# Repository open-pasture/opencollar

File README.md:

# OpenCollar

Open hardware virtual-fence collar. Off-the-shelf parts, open protocol, works with any software that speaks it.

Two collar types share as much as possible:

- **Rook** — base-station collar (LTE-M + GPS, larger battery)
- **Starling** — cheaper LoRa mesh-relay collar

## Repo map

| Path | What |
| --- | --- |
| [`docs/REPO-STRUCTURE.md`](docs/REPO-STRUCTURE.md) | Layout, old→new moves, conventions, firmware target split |
| [`docs/rook/`](docs/rook/) | Rook collar docs (flash / control / provision placeholders) |
| [`docs/starling/`](docs/starling/) | Starling collar docs (same) |
| [`docs/assembly/`](docs/assembly/) | Assembly pointers |
| [`docs/firmware/`](docs/firmware/) | Pilot firmware spec and Rook gap list |
| [`hardware/common/`](hardware/common/) | Shared CAD (`dims`, strap/clamp/insert), shared STLs |
| [`hardware/rook/`](hardware/rook/) | Rook Node V1 CAD, STLs, print profiles, fit audit |
| [`hardware/starling/`](hardware/starling/) | Starling skeleton (reuses common) |
| [`hardware/carrier/`](hardware/carrier/) | Carrier PCB |
| [`firmware/`](firmware/) | Zephyr firmware (see [`firmware/ARCHITECTURE.md`](firmware/ARCHITECTURE.md) for target layout) |
| [`protocol/`](protocol/) | Wire protocol and vectors |

### Design and build docs

- `docs/BUILD-LOG.md` — dated record of every step, result, and decision
- `docs/WELFARE-POLICY.md` — cue limits, auto shut-off, and welfare events (review thresholds before pulse)
- `docs/SHOCK-MODULE-INTERFACE.md` — reserved shock/pulse interface (side pods; OFF until named reviewer + Cody approve)
- `docs/PROTOTYPE-V0.md` — current state of the V0 prototype
- `docs/V1-DESIGN.md` — the V1 collar design and cost estimates
- `docs/MANUFACTURING.md` — how we get to 1,000 collars, and why FCC and carrier approval matter
- `docs/BOARD-DESIGN.md` — designing the custom board on a small budget
- `docs/DESIGN-PHASE.md` — board design toolchain and workflow (KiCad + SKiDL)
- `docs/COLLAR-FIRST-PRINCIPLES.md` — the slim collar worked out from first principles
- `docs/TEST-FIXTURE.md` — how every board gets tested, explained from zero, with pictures
- `docs/CARRIER-EXPLAINED.md` — every part on the carrier board, what it does, and where it sits in the collar
- `docs/STRATEGY.md` — product strategy and licensing
- `hardware/prototype-cart.md` — parts for the first prototype
- `hardware/orders-2026-09-26.md` — what was ordered and paid
- `hardware/tools.md` — tools for building a collar
- `hardware/bom.md` — parts list
- `hardware/photos/` — build photos

## Licence

OpenCollar is open so anyone can build, repair and improve their own collar.

| What | Licence | Folders |
| --- | --- | --- |
| Firmware, scripts and the protocol | [Apache-2.0](LICENSE) | `firmware/`, `protocol/`, and code anywhere else |
| Hardware and CAD (boards, enclosure, print files) | [CERN-OHL-W-2.0](LICENSES/CERN-OHL-W-2.0.txt) | `hardware/` |
| Docs, photos and renders | [CC BY 4.0](LICENSES/CC-BY-4.0.txt) | `docs/`, `hardware/photos/`, `hardware/*/renders/` |

In plain terms:

- **Firmware and protocol:** use them for anything, including closed products. Keep the copyright notice and [NOTICE](NOTICE).
- **Hardware:** build, sell and change the boards and the enclosure. If you ship a modified version of these design files, publish your changes to them under the same licence. Your own add-ons can stay closed.
- **Docs:** reuse them with credit to openpasture.

Third-party files keep their own licences: `firmware/boards/makerdiary/` (Apache-2.0, plus Nordic's 5-clause licence where its headers say so) and `firmware/third_party/monocypher/` (CC0 or BSD-2-Clause).

The names openpasture and OpenCollar and the openpasture logo aren't covered by these licences; see [NOTICE](NOTICE). Contributing: [CONTRIBUTING.md](CONTRIBUTING.md).

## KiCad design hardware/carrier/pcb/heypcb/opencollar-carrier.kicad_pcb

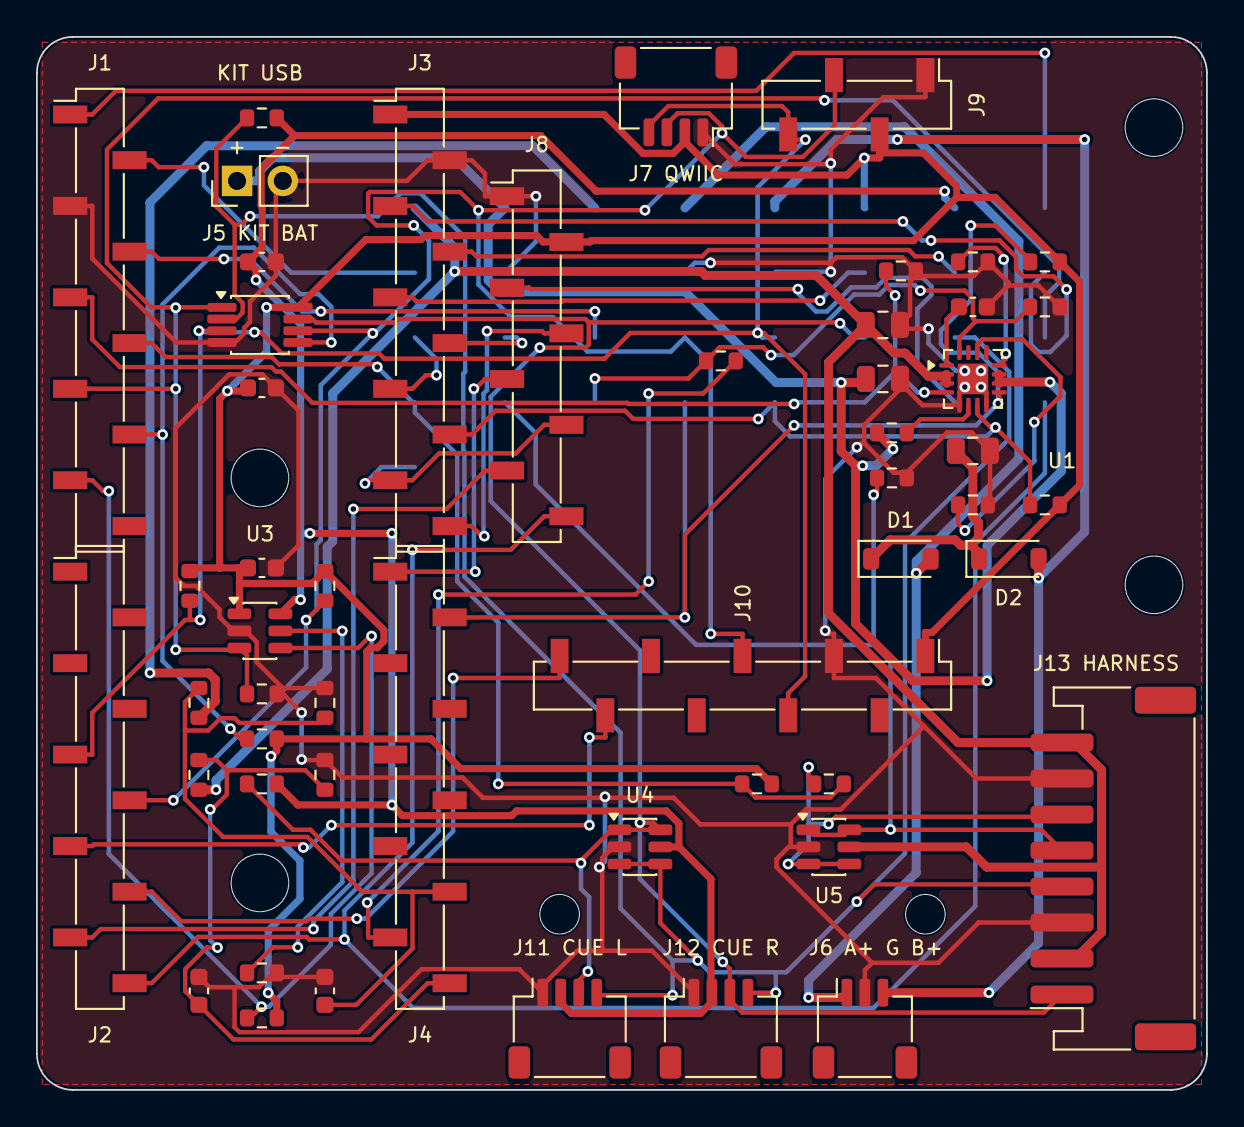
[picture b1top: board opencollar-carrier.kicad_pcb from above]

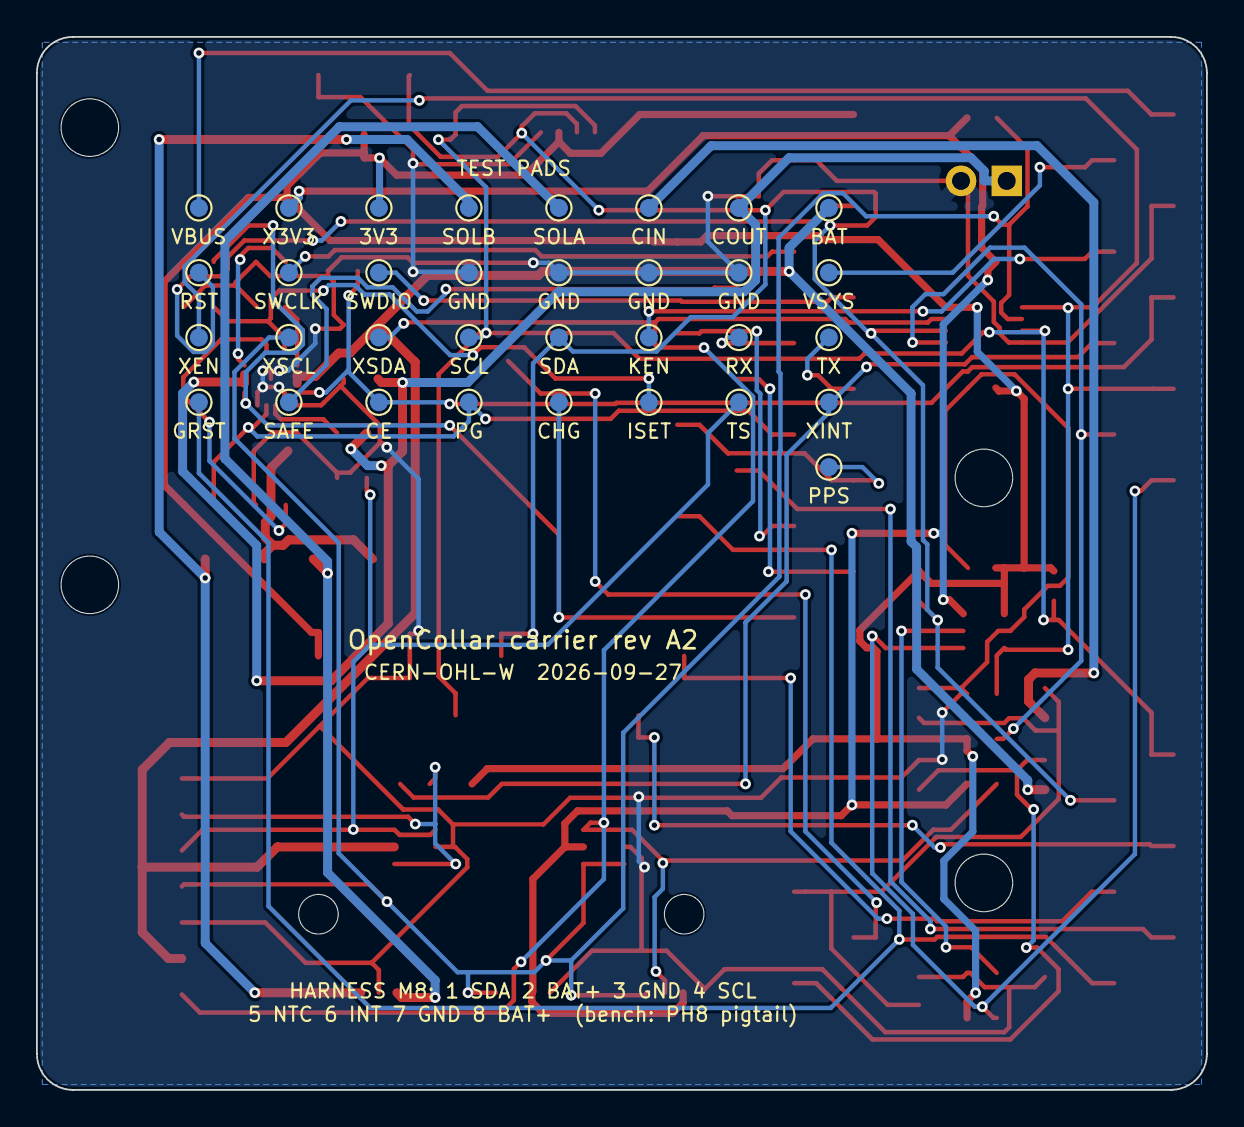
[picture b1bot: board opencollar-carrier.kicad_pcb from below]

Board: 2 copper layers, 65.0 x 58.5 mm, 91 parts (33 on the bottom side), 45 nets.

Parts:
C1: 10n; C_0603_1608Metric
C2, C3, C4: 10u/25V; C_0805_2012Metric
C5, C6, C7: 100n; C_0603_1608Metric
C8, C9: 1u; C_0603_1608Metric
D1, D2: B5819W; D_SOD-123
H1, H2, H3, H4: MountingHole; MountingHole_3.2mm_M3
H5, H6: MountingHole; MountingHole_2.2mm_M2
J1: Kit 1-10; PinSocket_1x10_P2.54mm_Vertical_SMD_Pin1Left
J2: Kit 11-20; PinSocket_1x10_P2.54mm_Vertical_SMD_Pin1Left
J3: Kit 40-31; PinSocket_1x10_P2.54mm_Vertical_SMD_Pin1Left
J4: Kit 30-21; PinSocket_1x10_P2.54mm_Vertical_SMD_Pin1Left
J5: Kit J2 feed; PinHeader_1x02_P2.54mm_Vertical
J6: Panels A/GND/B; JST_SH_SM03B-SRSS-TB_1x03-1MP_P1.00mm_Horizontal
J7: Qwiic spare; JST_SH_SM04B-SRSS-TB_1x04-1MP_P1.00mm_Horizontal
J8: M10S J5; PinSocket_1x08_P2.54mm_Vertical_SMD_Pin1Left
J9: M10S J3; PinSocket_1x04_P2.54mm_Vertical_SMD_Pin1Left
J10: ISM330; PinSocket_1x09_P2.54mm_Vertical_SMD_Pin1Left
J11: Cue L; JST_SH_SM04B-SRSS-TB_1x04-1MP_P1.00mm_Horizontal
J12: Cue R; JST_SH_SM04B-SRSS-TB_1x04-1MP_P1.00mm_Horizontal
J13: Harness M8; JST_PH_S8B-PH-SM4-TB_1x08-1MP_P2.00mm_Horizontal
R1, R5, R17: 10k; R_0603_1608Metric
R2: 887; R_0603_1608Metric
R3: 3.24k; R_0603_1608Metric
R4: 71.5k; R_0603_1608Metric
R6, R7, R8, R13, R16, R20, R21, R23: 100k; R_0603_1608Metric
R9, R10, R11: 1M; R_0603_1608Metric
R12: 200k; R_0603_1608Metric
R14, R15, R18, R19: 4.7k; R_0603_1608Metric
R22: 1k; R_0603_1608Metric
TP1: BAT; TestPoint_Pad_D1.0mm
TP2: CHG_OUT; TestPoint_Pad_D1.0mm
TP3: CHG_IN; TestPoint_Pad_D1.0mm
TP4: SOLAR_A; TestPoint_Pad_D1.0mm
TP5: SOLAR_B; TestPoint_Pad_D1.0mm
TP6: 3V3; TestPoint_Pad_D1.0mm
TP7: EXT_3V3; TestPoint_Pad_D1.0mm
TP8: KIT_VBUS; TestPoint_Pad_D1.0mm
TP9: KIT_VSYS; TestPoint_Pad_D1.0mm
TP10, TP11, TP12, TP13: GND; TestPoint_Pad_D1.0mm
TP14: SWDIO; TestPoint_Pad_D1.0mm
TP15: SWCLK; TestPoint_Pad_D1.0mm
TP16: RESET; TestPoint_Pad_D1.0mm
TP17: UART_TX; TestPoint_Pad_D1.0mm
TP18: UART_RX; TestPoint_Pad_D1.0mm
TP19: KIT_EN; TestPoint_Pad_D1.0mm
TP20: I2C_SDA; TestPoint_Pad_D1.0mm
TP21: I2C_SCL; TestPoint_Pad_D1.0mm
TP22: EXT_SDA; TestPoint_Pad_D1.0mm
TP23: EXT_SCL; TestPoint_Pad_D1.0mm
TP24: EXT_EN; TestPoint_Pad_D1.0mm
TP25: EXT_INT; TestPoint_Pad_D1.0mm
TP26: TS; TestPoint_Pad_D1.0mm
TP27: ISET; TestPoint_Pad_D1.0mm
TP28: CHG_STAT; TestPoint_Pad_D1.0mm
TP29: CHG_PGOOD; TestPoint_Pad_D1.0mm
TP30: CHG_CE; TestPoint_Pad_D1.0mm
TP31: GNSS_SAFEBOOT; TestPoint_Pad_D1.0mm
TP32: GNSS_RESET_N; TestPoint_Pad_D1.0mm
TP33: GNSS_PPS; TestPoint_Pad_D1.0mm
U1: BQ24074RGT; VQFN-16-1EP_3x3mm_P0.5mm_EP1.68x1.68mm
U2: TCA4307; VSSOP-8_3x3mm_P0.65mm
U3: TPS2553; SOT-23-6
U4, U5: USBLC6-2SC6; SOT-23-6

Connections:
3V3: C7.1, C8.1, J3.1, J7.2, J8.2, J9.2, J10.1, R7.2, R8.2, R14.2, R15.2, R17.2, R21.2, R23.2, TP6.1, U2.8, U3.1
BAT: C4.1, J13.2, J13.8, R9.1, TP1.1, U1.2, U1.3, U5.5
CHG_CE: J1.5, R6.1, TP30.1, U1.4
CHG_IN: C2.1, D1.1, D2.1, R11.1, TP3.1, U1.13
CHG_OUT: C3.1, J5.1, R1.1, TP2.1, U1.10, U1.11
CHG_PGOOD: J3.8, R8.1, TP29.1, U1.7
CHG_STAT: J4.2, R7.1, TP28.1, U1.9
EXT_3V3: C9.1, J11.2, J12.2, R18.2, R19.2, TP7.1, U3.6, U4.5
EXT_EN: J1.7, R16.1, TP24.1, U2.1, U3.3
EXT_FAULT: J1.9, R21.1, U3.4
EXT_INT: J1.6, R22.2, R23.1, TP25.1
EXT_INT_RAW: J13.6, R22.1, U5.3, U5.4
EXT_READY: J1.8, R17.1, U2.5
EXT_SCL: J11.4, J12.4, J13.4, R19.1, TP23.1, U2.2, U4.3, U4.4
EXT_SDA: J11.3, J12.3, J13.1, R18.1, TP22.1, U2.7, U4.1, U4.6
GND: C1.2, C2.2, C3.2, C4.2, C5.2, C6.2, C7.2, C8.2, C9.2, J1.3, J3.2, J5.2, J6.2, J7.1, J8.1, J9.1, J10.3, J11.1, J12.1, J13.3, J13.7, R2.2, R3.2, R4.2, R5.2, R6.2, R10.2, R12.2, R16.2, R20.2, TP10.1, TP11.1, TP12.1, TP13.1, U1.5, U1.8, U1.17, U2.4, U3.2, U4.2, U5.2
GNSS_EXTINT: J2.9, J8.7
GNSS_PPS: J3.9, J8.6, TP33.1
GNSS_RESET_N: J2.10, J8.8, TP32.1
GNSS_RXD: J4.1, J8.5
GNSS_SAFEBOOT: J8.3, TP31.1
GNSS_TXD: J3.10, J8.4
I2C_SCL: J2.5, J7.4, J9.4, J10.4, R15.1, TP21.1, U2.3
I2C_SDA: J2.6, J7.3, J9.3, J10.5, R14.1, TP20.1, U2.6
IMU_INT1: J2.7, J10.8
IMU_INT2: J2.8, J10.9
ISET: R2.1, R13.1, TP27.1, U1.16
ISET_SENSE: J4.9, R13.2
KIT_EN: J1.4, TP19.1
KIT_VBUS: J1.1, TP8.1
KIT_VSYS: J1.2, TP9.1
unnamed: R1.2, U1.6
unnamed: R3.1, U1.12
unnamed: R4.1, U1.14
unnamed: R20.1, U3.5
RESET: J3.3, TP16.1
SOLAR_A: D1.2, J6.1, TP4.1
SOLAR_B: D2.2, J6.3, TP5.1
SWCLK: J3.4, TP15.1
SWDIO: J3.5, TP14.1
TS: C1.1, J13.5, R5.1, TP26.1, U1.1, U5.1, U5.6
UART_RX: J3.6, TP18.1
UART_TX: J3.7, TP17.1
VBAT_SENSE: C5.1, J4.10, R9.2, R10.1
VIN_SENSE: C6.1, J4.8, R11.2, R12.1

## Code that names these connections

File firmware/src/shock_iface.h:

/*
 * Shock / pulse module — names and states only.
 *
 * Reservation: docs/SHOCK-MODULE-INTERFACE.md, protocol/registry.md.
 * Placement (Cody): side pods. This header must not grow functions that
 * drive any output. No welfare reviewer is named yet — module stays OFF
 * in all builds until one is named and Cody approves. Dual enable /
 * GATE_LATCH / pulse_grant are proposed, awaiting Cody. Default is off;
 * not_fitted / unknown means no path may drive HV.
 */
#ifndef OPENCOLLAR_SHOCK_IFACE_H
#define OPENCOLLAR_SHOCK_IFACE_H

/* Firmware-internal / registry module states. Wire: emit health.module only
 * when fitted; omit the block when not_fitted (servers must not treat absence
 * as ok). Do not reuse the v2 fence "armed" status bit for the module. */
enum shock_module_state {
	SHOCK_NOT_FITTED = 0,
	SHOCK_FITTED_DISABLED = 1,
	SHOCK_FITTED_READY = 2,
	SHOCK_FAULT = 3,
	SHOCK_KILLED = 4,
};

/* Proposed fault names; any fault keeps HV off until a person re-enables
 * (not welfare caretaker rearm / cue_clear_shutoff). */
enum shock_fault {
	SHOCK_FAULT_NONE = 0,
	SHOCK_FAULT_OPEN_ELECTRODE = 1,
	SHOCK_FAULT_SHORT = 2,
	SHOCK_FAULT_OVER_CURRENT = 3,
	SHOCK_FAULT_NO_CONTACT = 4,
	SHOCK_FAULT_OVER_TEMP = 5,
	SHOCK_FAULT_BAD_ID = 6,
};

/* Stable wire / registry string names (v1 JSON style). No v1 "present":
 * health.module exists only when fitted. */
#define SHOCK_CAP_NAME "shock_module"
#define SHOCK_PULSE_GRANT_NAME "pulse_grant"
#define SHOCK_CUE_KIND_PULSE "pulse"
#define SHOCK_REPORT_HEALTH_MODULE "module"
#define SHOCK_REPORT_HW_REV "hw_rev"
#define SHOCK_REPORT_STATE "state"
#define SHOCK_REPORT_FAULT "fault"

#define SHOCK_STATE_NAME_NOT_FITTED "not_fitted"
#define SHOCK_STATE_NAME_FITTED_DISABLED "fitted_disabled"
#define SHOCK_STATE_NAME_FITTED_READY "fitted_ready"
#define SHOCK_STATE_NAME_FAULT "fault"
#define SHOCK_STATE_NAME_KILLED "killed"

#define SHOCK_FAULT_NAME_OPEN_ELECTRODE "open_electrode"
#define SHOCK_FAULT_NAME_SHORT "short"
#define SHOCK_FAULT_NAME_OVER_CURRENT "over_current"
#define SHOCK_FAULT_NAME_NO_CONTACT "no_contact"
#define SHOCK_FAULT_NAME_OVER_TEMP "over_temp"
#define SHOCK_FAULT_NAME_BAD_ID "bad_id"

/* Logical connector nets (MCU pin numbers TBD; see interface doc).
 * All HV / driver / HW current limit live on the module; main board has only
 * these LV signals. GATE_LATCH is an MCU output: firmware arms a one-shot
 * latch on the module (cleared on reset); not firmware-independent.
 * Protection is pulse_grant + module HW current limit + kill line. */
#define SHOCK_NET_SENSE "SENSE"
#define SHOCK_NET_I2C_SDA "I2C_SDA"
#define SHOCK_NET_I2C_SCL "I2C_SCL"
#define SHOCK_NET_HV_EN "HV_EN"
#define SHOCK_NET_KILL "KILL"
#define SHOCK_NET_FAULT "FAULT"
#define SHOCK_NET_GND "GND"
#define SHOCK_NET_BAT "BAT"
#define SHOCK_NET_GATE_LATCH "GATE_LATCH"
#define SHOCK_NET_KILL_SENSE "KILL_SENSE"

#endif

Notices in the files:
hardware/carrier/pcb/heypcb/opencollar-carrier.kicad_pcb:
CERN-OHL-W  2026-09-27
